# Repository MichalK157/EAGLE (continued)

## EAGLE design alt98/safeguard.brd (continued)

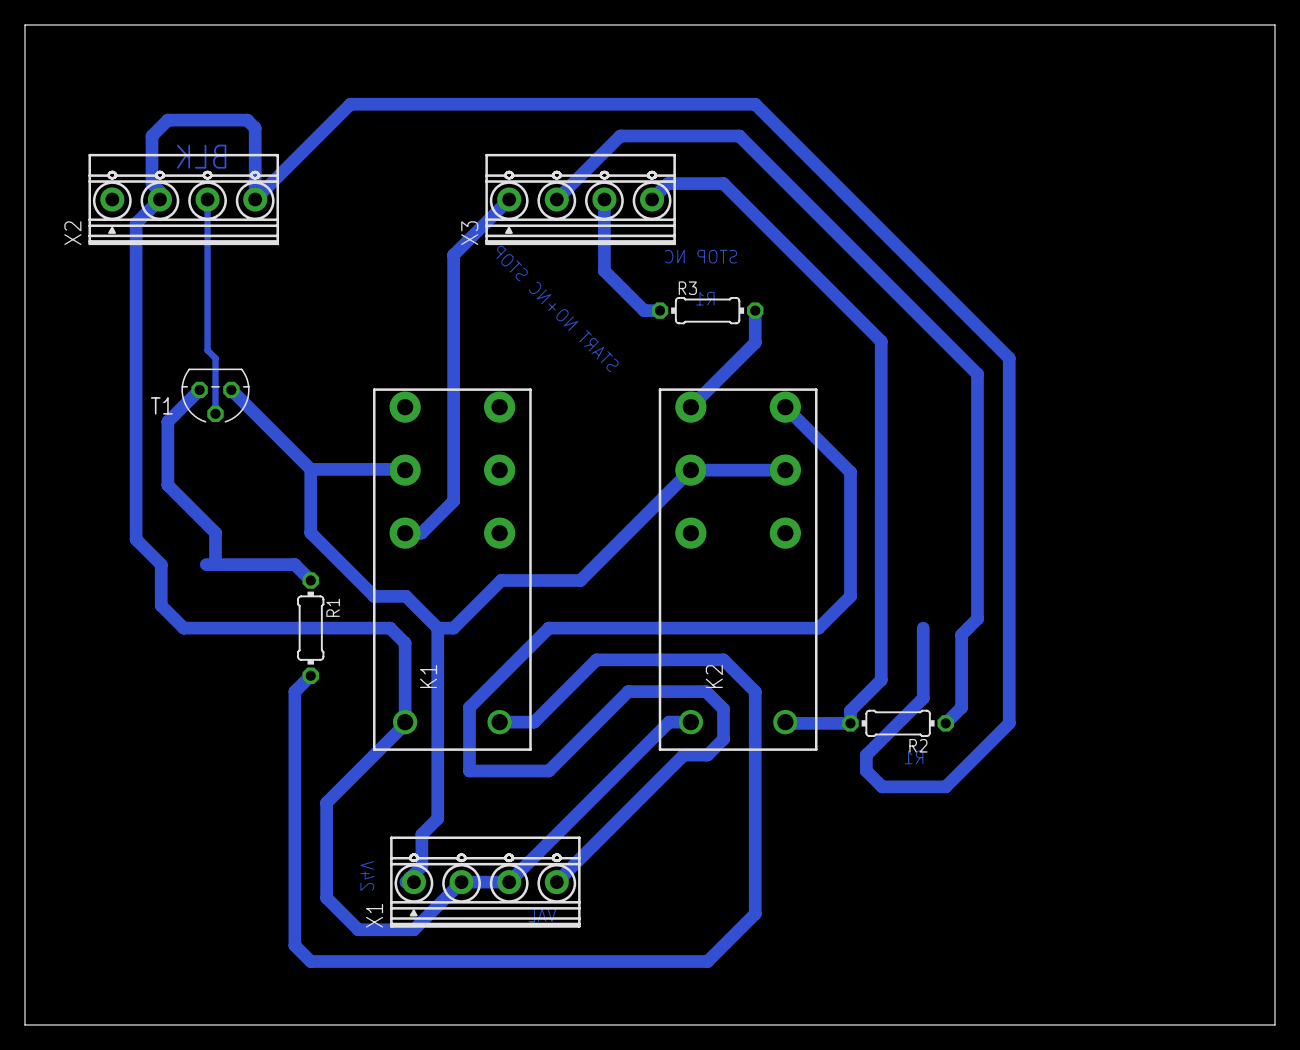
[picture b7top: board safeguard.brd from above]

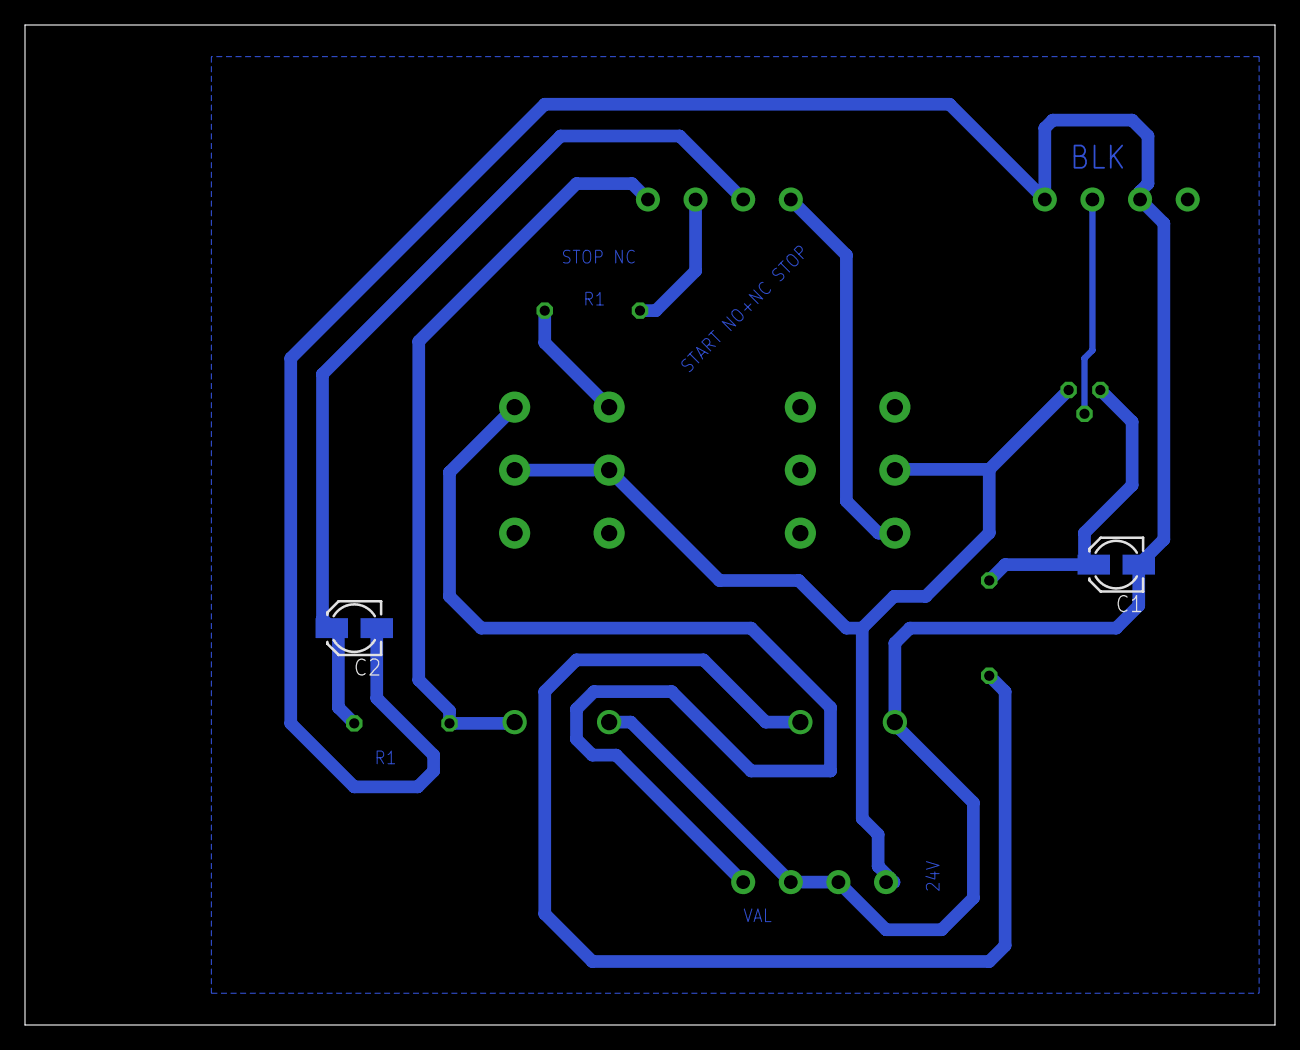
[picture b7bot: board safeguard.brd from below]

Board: 2 copper layers, 100.0 x 80.0 mm, 11 parts (2 on the bottom side), 11 nets.

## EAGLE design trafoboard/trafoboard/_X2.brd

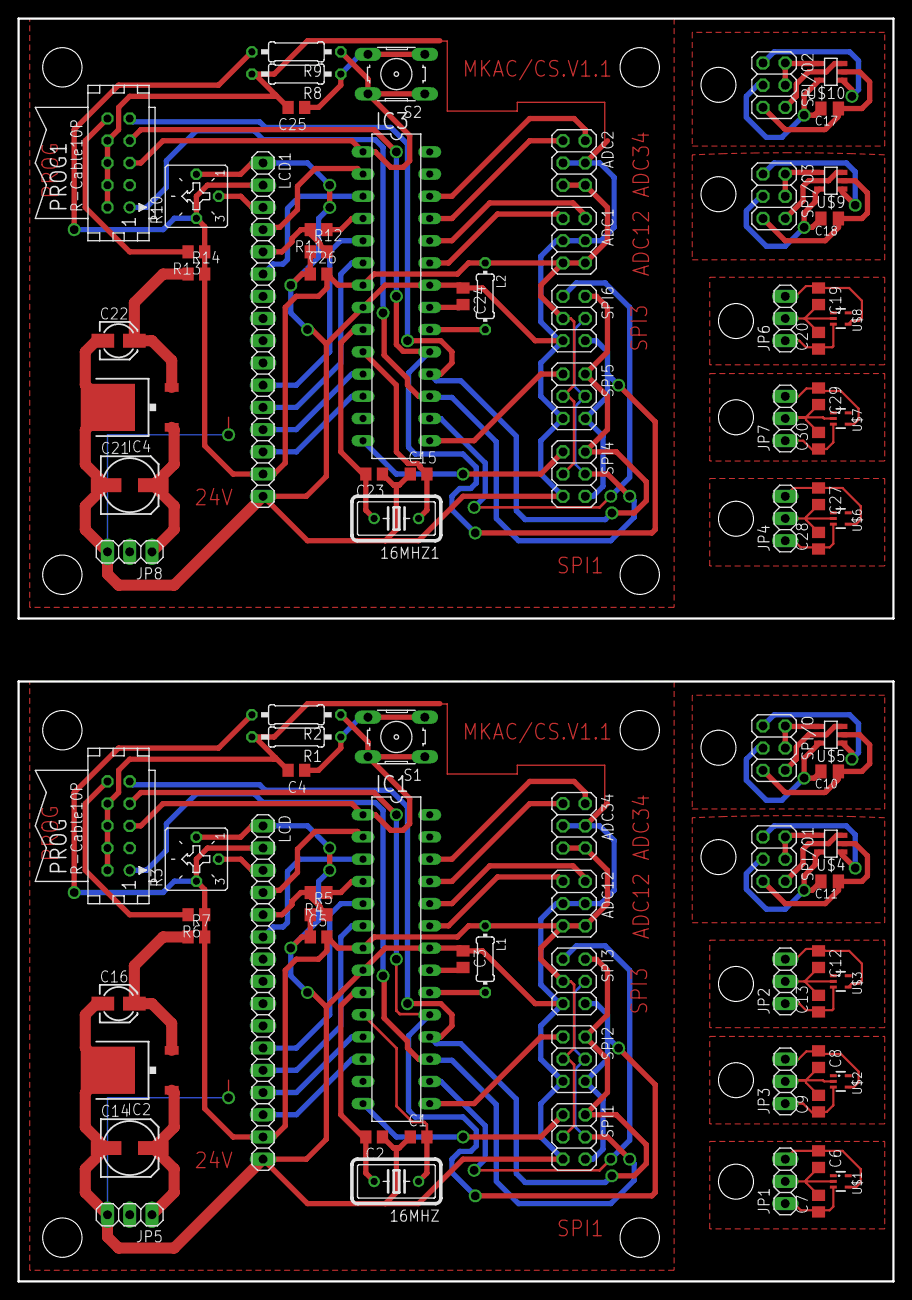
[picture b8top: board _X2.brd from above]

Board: 2 copper layers, 100.0 x 144.3 mm, 90 parts (0 on the bottom side), 98 nets.

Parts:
16MHZ, 16MHZ1: HC18U-V
ADC1, ADC2, ADC12, ADC34: 2X03
C1, C2, C15, C23: 22P; C0805
C3, C4, C5, C24, C25, C26: 100n; C0805
C6, C7, C8, C9, C12, C13, C19, C20, C27, C28, C29, C30: 220P; C0805
C10, C11, C17, C18: 100nF; C0805K
C14, C21: 10u; 153CLV-0605
C16, C22: 1u; 153CLV-0405
IC1, IC3: MEGA8-P; DIL28-3
IC2, IC4: 7805DT; TO252
JP1, JP2, JP3, JP4, JP5, JP6, JP7, JP8: 1X03
L1, L2: 10u; 0204/7
LCD, LCD1: 1X16
PROG, PROG1: CON10
R1, R8: 100; 0207/10
R2, R9: 10k; 0207/10
R3, R10: CT6
R4, R5, R6, R7, R11, R12, R13, R14: 0; R0805
S1, S2: B3F-10XX
SPI1, SPI2, SPI3, SPI4, SPI5, SPI6: 2X03
SPI/O, SPI/O1, SPI/O2, SPI/O3: 2X03
U$1, U$2, U$3, U$6, U$7, U$8: SC70-5L
U$4, U$5, U$9, U$10: TC77-3.3MCTTR; SOT23-5

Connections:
5V: ADC12.5, ADC12.6, ADC34.5, ADC34.6, C5.2, IC1.7, L1.1, LCD.2, LCD.15, R2.2, R3.E, R6.1, R7.2, SPI1.3, SPI2.3, SPI3.3
5V1: ADC1.5, ADC1.6, ADC2.5, ADC2.6, C26.2, IC3.7, L2.1, LCD1.2, LCD1.15, R9.2, R10.E, R13.1, R14.2, SPI4.3, SPI5.3, SPI6.3
ADC1: ADC12.1, IC1.23
ADC2: ADC12.2, IC1.24
ADC3: ADC34.1, IC1.25
ADC4: ADC34.2, IC1.26
ADC5: ADC2.1, IC3.25
ADC6: ADC1.1, IC3.23
ADC7: ADC1.2, IC3.24
ADC8: ADC2.2, IC3.26
D1: IC3.5, LCD1.11
D2: IC3.6, LCD1.12
D3: IC3.11, LCD1.13
D4: IC1.5, LCD.11
D5: IC1.6, LCD.12
D6: IC1.11, LCD.13
D7: IC1.12, LCD.14
D8: IC3.12, LCD1.14
E: IC1.3, LCD.6
E1: IC3.3, LCD1.6
GND: ADC12.3, ADC12.4, ADC34.3, ADC34.4, C1.1, C2.1, C3.1, C4.2, C5.1, C14.-, C16.-, IC1.8, IC1.22, IC2.3, JP5.3, LCD.1, LCD.16, PROG.2, PROG.4, PROG.6, PROG.8, R1.2, R3.A, R5.1, SPI1.5, SPI2.5, SPI3.5
GND1: ADC1.3, ADC1.4, ADC2.3, ADC2.4, C15.1, C21.-, C22.-, C23.1, C24.1, C25.2, C26.1, IC3.8, IC3.22, IC4.3, JP8.3, LCD1.1, LCD1.16, PROG1.2, PROG1.4, PROG1.6, PROG1.8, R8.2, R10.A, R12.1, SPI4.5, SPI5.5, SPI6.5
MISO: IC1.18, PROG.9, SPI1.2, SPI2.2, SPI3.2
MISO1: IC3.18, PROG1.9, SPI4.2, SPI5.2, SPI6.2
MOSI: IC1.17, PROG.1, SPI1.4, SPI2.4, SPI3.4
MOSI1: IC3.17, PROG1.1, SPI4.4, SPI5.4, SPI6.4
unnamed: 16MHZ.2, C2.2, IC1.9
unnamed: 16MHZ.1, C1.2, IC1.10
unnamed: IC1.20, L1.2
unnamed: C3.2, IC1.21
unnamed: C4.1, R1.1, S1.3, S1.4
unnamed: LCD.5, R4.2, R5.2
unnamed: C13.1, JP2.1, U$3.3
unnamed: LCD.3, R3.S
unnamed: C12.2, C13.2, JP2.2, U$3.2
unnamed: C12.1, JP2.3, U$3.4
unnamed: PROG.10, R6.2
unnamed: C7.1, JP1.1, U$1.3
unnamed: C6.2, C7.2, JP1.2, U$1.2
unnamed: C6.1, JP1.3, U$1.4
unnamed: C9.1, JP3.1, U$2.3
unnamed: C8.2, C9.2, JP3.2, U$2.2
unnamed: C8.1, JP3.3, U$2.4
unnamed: C10.2, SPI/O.3, U$5.5
unnamed: C10.1, SPI/O.5, U$5.2
unnamed: SPI/O.1, U$5.1
unnamed: C16.+, IC2.2, R7.1
unnamed: SPI/O.2, SPI/O.4, U$5.4
unnamed: C14.+, IC2.1, JP5.1
unnamed: SPI/O.6, U$5.3
unnamed: C11.2, SPI/O1.3, U$4.5
unnamed: C11.1, SPI/O1.5, U$4.2
unnamed: 16MHZ1.2, C23.2, IC3.9
unnamed: SPI/O1.1, U$4.1
unnamed: SPI/O1.2, SPI/O1.4, U$4.4
unnamed: SPI/O1.6, U$4.3
unnamed: 16MHZ1.1, C15.2, IC3.10
unnamed: IC3.20, L2.2
unnamed: C24.2, IC3.21
unnamed: C25.1, R8.1, S2.3, S2.4
unnamed: LCD1.3, R10.S
unnamed: LCD1.5, R11.2, R12.2
unnamed: C20.1, JP6.1, U$8.3
unnamed: C19.2, C20.2, JP6.2, U$8.2
unnamed: C19.1, JP6.3, U$8.4
unnamed: C28.1, JP4.1, U$6.3
unnamed: C27.2, C28.2, JP4.2, U$6.2
unnamed: C27.1, JP4.3, U$6.4
unnamed: C30.1, JP7.1, U$7.3
unnamed: C29.2, C30.2, JP7.2, U$7.2
unnamed: C29.1, JP7.3, U$7.4
unnamed: PROG1.10, R13.2
unnamed: C22.+, IC4.2, R14.1
unnamed: C21.+, IC4.1, JP8.1
unnamed: C17.2, SPI/O2.3, U$10.5
unnamed: C17.1, SPI/O2.5, U$10.2
unnamed: SPI/O2.1, U$10.1
unnamed: SPI/O2.2, SPI/O2.4, U$10.4
unnamed: SPI/O2.6, U$10.3
unnamed: C18.2, SPI/O3.3, U$9.5
unnamed: C18.1, SPI/O3.5, U$9.2
unnamed: SPI/O3.1, U$9.1
unnamed: SPI/O3.2, SPI/O3.4, U$9.4
unnamed: SPI/O3.6, U$9.3
RS: IC1.2, LCD.4
RS1: IC3.2, LCD1.4
RST: IC1.1, PROG.5, R2.1, S1.1, S1.2
RST1: IC3.1, PROG1.5, R9.1, S2.1, S2.2
RW: IC1.4, R4.1
RW1: IC3.4, R11.1
SCK: IC1.19, PROG.7, SPI1.6, SPI2.6, SPI3.6
SCK1: IC3.19, PROG1.7, SPI4.6, SPI5.6, SPI6.6
SS1: IC1.14, SPI1.1
SS2: IC1.15, SPI2.1
SS3: IC1.16, SPI3.1
SS4: IC3.14, SPI4.1
SS5: IC3.15, SPI5.1
SS6: IC3.16, SPI6.1

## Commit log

2018-10-30 All pjoject
